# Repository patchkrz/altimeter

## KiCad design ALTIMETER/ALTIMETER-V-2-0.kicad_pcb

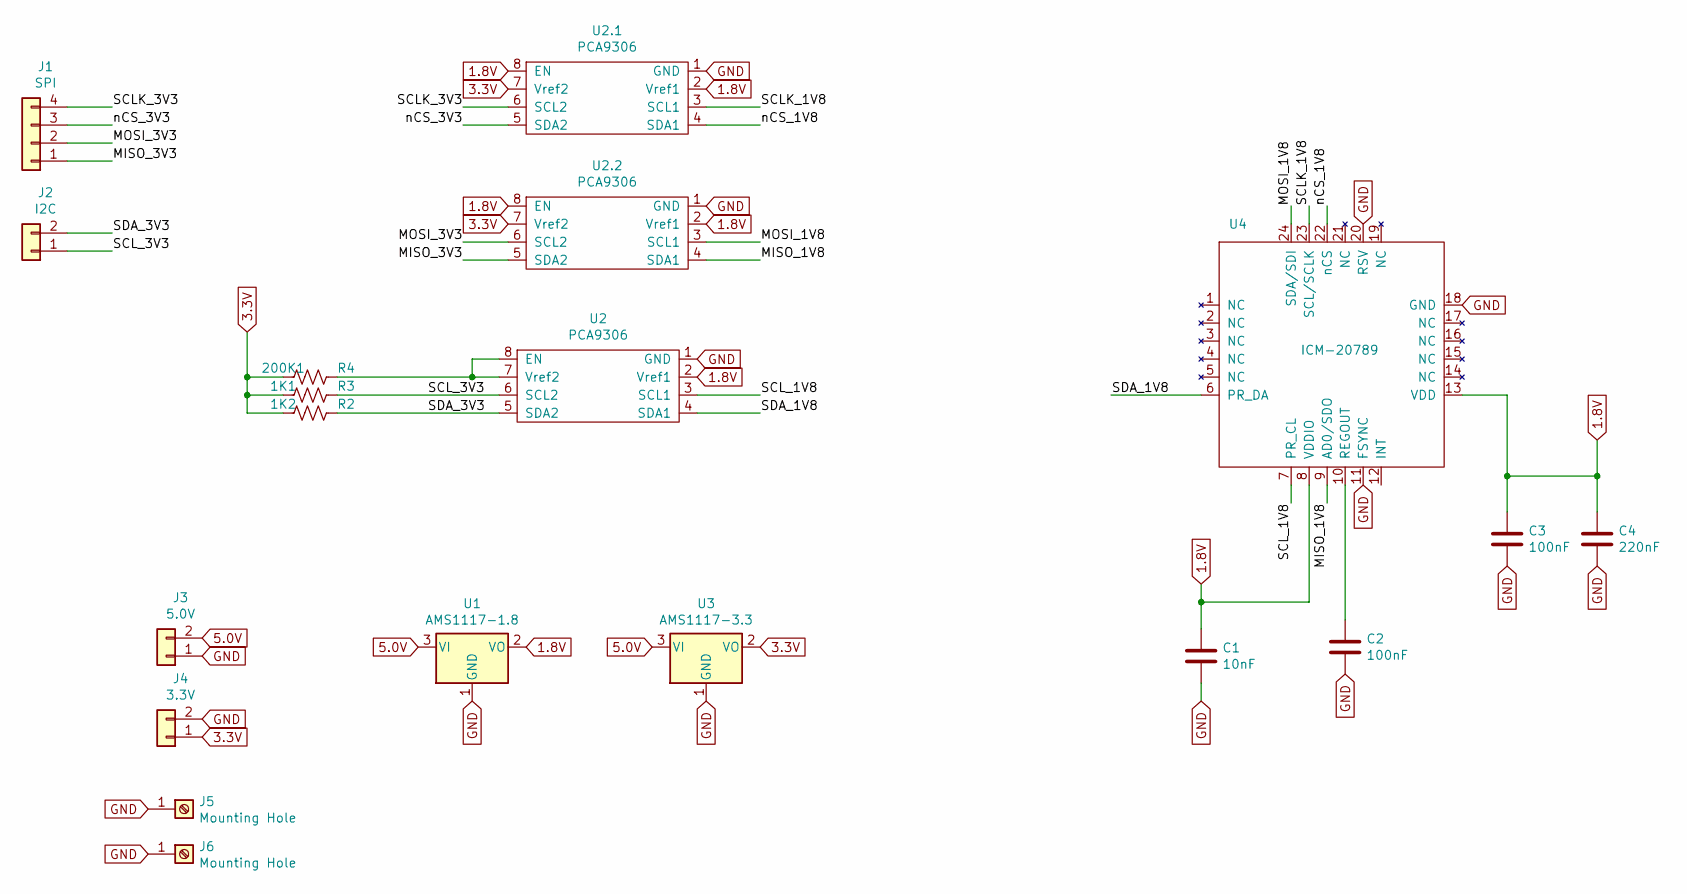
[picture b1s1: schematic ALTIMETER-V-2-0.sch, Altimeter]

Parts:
1K1: R3; R_1206_3216Metric
1K2: R2; R_1206_3216Metric
200K1: R4; R_1206_3216Metric
C1: 10nF; C_0805_2012Metric
C2, C3: 100nF; C_0805_2012Metric
C4: 220nF; C_0805_2012Metric
J1: SPI; JST_XH_S04B-XH-A_1x04_P2.50mm_Horizontal
J2: I2C; JST_XH_S02B-XH-A-1_1x02_P2.50mm_Horizontal
J3: 5.0V; JST_XH_S02B-XH-A_1x02_P2.50mm_Horizontal
J4: 3.3V; JST_XH_S02B-XH-A_1x02_P2.50mm_Horizontal
J5, J6: Mounting Hole; MountingHole_3.2mm_M3_DIN965_Pad
U1: AMS1117-1.8; SOT-223-3_TabPin2
U2, U2.1, U2.2: PCA9306; VSSOP-8_2.3x2mm_P0.5mm
U3: AMS1117-3.3; SOT-223-3_TabPin2
U4: ICM-20789; DEHA-LGA-24

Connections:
1.8V: C1.1, C3.1, C4.1, U1.2 (VO), U2.2 (Vref1), U2.1.2 (Vref1), U2.1.8 (EN), U2.2.2 (Vref1), U2.2.8 (EN), U4.8 (VDDIO), U4.13 (VDD)
3.3V: 1K1.2, 1K2.2, 200K1.2, J4.1, U2.1.7 (Vref2), U2.2.7 (Vref2), U3.2 (VO)
5.0V: J3.2, U1.3 (VI), U3.3 (VI)
/MISO_1V8: U2.2.4 (SDA1), U4.9 (AD0/SDO)
/MISO_3V3: J1.1, U2.2.5 (SDA2)
/MOSI_1V8: U2.2.3 (SCL1), U4.24 (SDA/SDI)
/MOSI_3V3: J1.2, U2.2.6 (SCL2)
/SCLK_1V8: U2.1.3 (SCL1), U4.23 (SCL/SCLK)
/SCLK_3V3: J1.4, U2.1.6 (SCL2)
/SCL_1V8: U2.3 (SCL1), U4.7 (PR_CL)
/SCL_3V3: 1K1.1, J2.1, U2.6 (SCL2)
/SDA_1V8: U2.4 (SDA1), U4.6 (PR_DA)
/SDA_3V3: 1K2.1, J2.2, U2.5 (SDA2)
/nCS_1V8: U2.1.4 (SDA1), U4.22 (nCS)
/nCS_3V3: J1.3, U2.1.5 (SDA2)
GND: C1.2, C2.2, C3.2, C4.2, J3.1, J4.2, J5.1, J6.1, U1.1 (GND), U2.1 (GND), U2.1.1 (GND), U2.2.1 (GND), U3.1 (GND), U4.11 (FSYNC), U4.18 (GND), U4.20 (RSV)
unnamed: 200K1.1, U2.7 (Vref2), U2.8 (EN)
unnamed: C2.1, U4.10 (REGOUT)

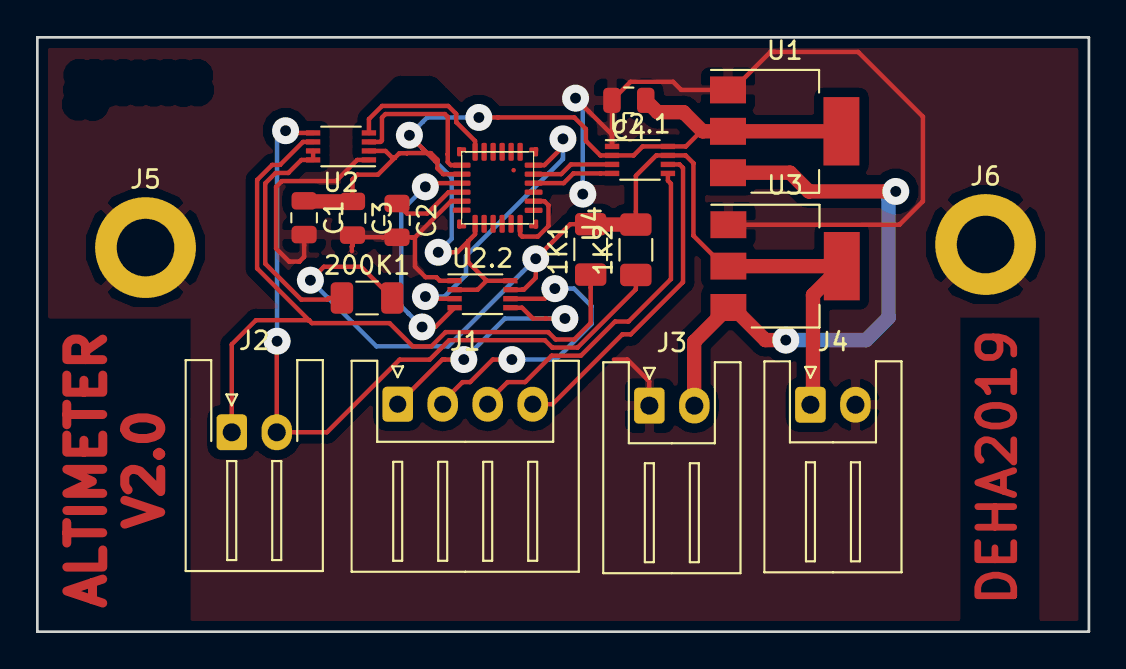
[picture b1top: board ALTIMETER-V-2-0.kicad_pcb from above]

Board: 2 copper layers, 58.4 x 33.0 mm, 19 parts (0 on the bottom side), 18 nets.
